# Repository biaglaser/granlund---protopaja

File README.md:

This project was completed for a course at Aalto University and its problem was proposed by 
Granlund OY. It focuses on the development and implementation of an Internet of Things 
(IoT) device designed to monitor structural parameters of network base stations, 
often located in remote and hard-to-reach areas. The device was developed during 
Aalto University’s Protopaja course with the aim is to digitize and automate the 
monitoring and analysis of various structures, products, and services. The primary 
objective was to create an energy-efficient, long-lasting IoT device capable of 
measuring the structural conditions of the station towers and display the collected, 
clean data to the user. 

Utilizing wireless sensor stations, the device aims to capture real-time data and transmit it 
to a microprocessor via Bluetooth. Data is then sent to a cloud-based server via a 
mobile network, where it is processed, stored, and displayed through a user 
interface. This allows for real-time statistical display, anomaly detection, and 
predictive maintenance alerts.

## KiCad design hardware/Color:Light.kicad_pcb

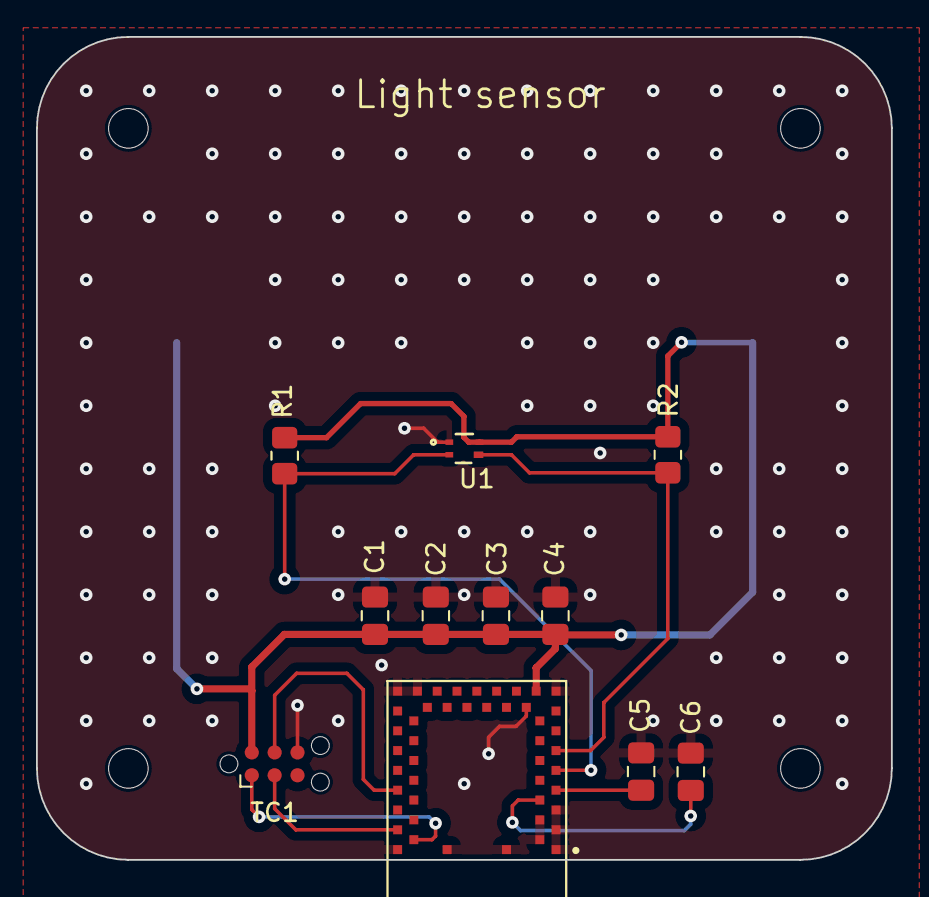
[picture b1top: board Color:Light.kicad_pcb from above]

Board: 2 copper layers, 47.5 x 45.7 mm, 12 parts (1 on the bottom side), 9 nets.

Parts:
BT1: BRX1-2477-SM; BAT_BRX1-2477-SM
C1, C3: 1u; C_0805_2012Metric_Pad1.18x1.45mm_HandSolder
C2: 10u; C_0805_2012Metric_Pad1.18x1.45mm_HandSolder
C4: 100n; C_0805_2012Metric_Pad1.18x1.45mm_HandSolder
C5, C6: 12p; C_0805_2012Metric_Pad1.18x1.45mm_HandSolder
R1, R2: 4.7k; R_0805_2012Metric_Pad1.20x1.40mm_HandSolder
TC1: TC2030-IDC; Tag-Connect_TC2030-IDC-NL_2x03_P1.27mm_Vertical
U1: VEML3328; SMD_L3328_VIS
U2: BMD-301-A-R

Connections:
/RESET: TC1.4, U2.39 (P0.21)
/SCL: R2.2, U1.3, U2.11 (P0.30)
/SDA: R1.2, U1.2, U2.9 (P0.28)
/SW_CLK: TC1.3, U2.43 (SWCLK)
/SW_DIO: TC1.1, U2.44 (SWDIO)
GND: BT1.-, C1.2, C2.2, C3.2, C4.2, C5.2, C6.2, TC1.6, U1.1, U2.1 (GND), U2.2 (GND), U2.3 (GND), U2.4 (GND), U2.5 (GND), U2.16 (GND), U2.18 (GND), U2.29 (GND), U2.30 (GND), U2.45 (GND), U2.46 (GND), U2.47 (GND)
unnamed: C6.1, U2.6 (P0.25)
unnamed: C5.1, U2.7 (P0.26)
VCC: BT1.1+, BT1.2+, C1.1, C2.1, C3.1, C4.1, R1.1, R2.1, TC1.2, U1.4, U2.17 (VCC)

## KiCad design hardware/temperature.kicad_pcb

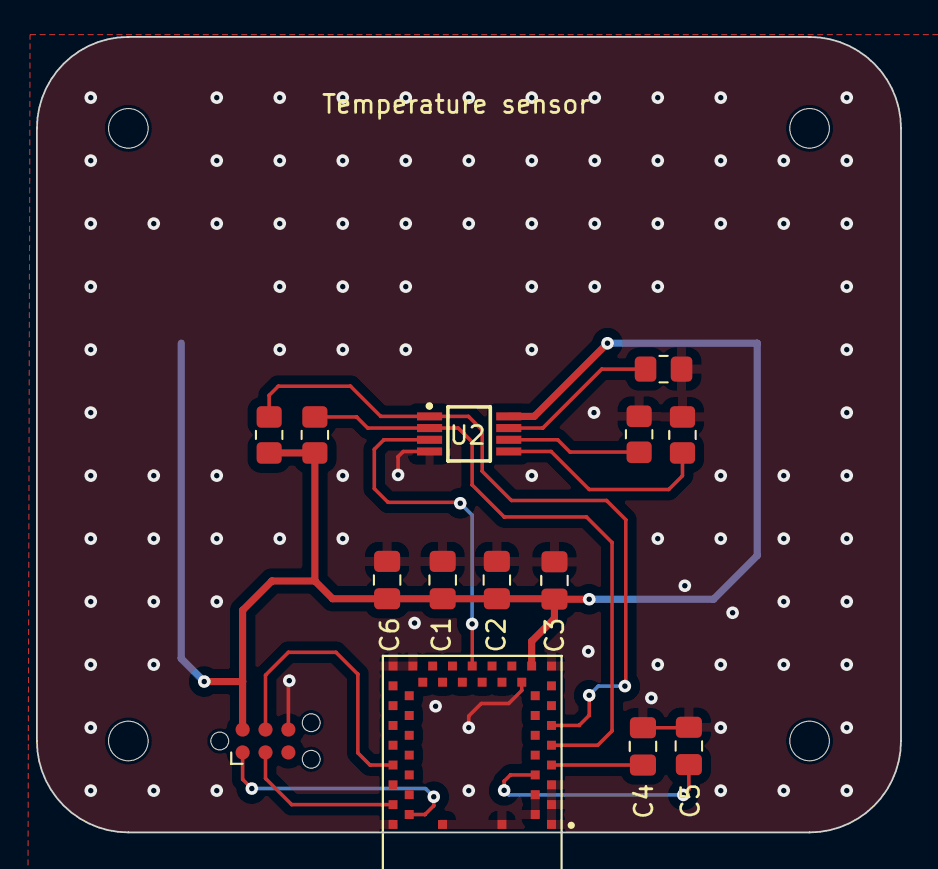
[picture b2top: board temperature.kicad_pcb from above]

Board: 2 copper layers, 48.0 x 44.2 mm, 15 parts (1 on the bottom side), 13 nets.

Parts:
BT2: BRX1-2477-SM; BAT_BRX1-2477-SM
C1: 10u; C_0805_2012Metric_Pad1.18x1.45mm_HandSolder
C2, C6: 1u; C_0805_2012Metric_Pad1.18x1.45mm_HandSolder
C3: 100n; C_0805_2012Metric_Pad1.18x1.45mm_HandSolder
C4, C5: 12p; C_0805_2012Metric_Pad1.18x1.45mm_HandSolder
R6, R7, R8, R9: 4.7k; R_0805_2012Metric_Pad1.20x1.40mm_HandSolder
R10: 4.7K; R_0805_2012Metric_Pad1.20x1.40mm_HandSolder
TC2: TC2030-IDC; Tag-Connect_TC2030-IDC-NL_2x03_P1.27mm_Vertical
U1: BMD-301-A-R
U2: MCP9808T-E/MS; SOP65P490X110-8N

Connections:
/ALERT: U1.23 (P0.07), U2.3 (ALERT)
/RESET: TC2.4, U1.39 (P0.21)
/SCL: R9.2, U1.11 (P0.30), U2.1 (SDA)
/SDA: R10.2, U1.9 (P0.28), U2.2 (SCL)
/SW_CLK: TC2.3, U1.43 (SWCLK)
/SW_DIO: TC2.1, U1.44 (SWDIO)
GND: BT2.-, C1.2, C2.2, C3.2, C4.2, C5.2, C6.1, R6.2, R7.2, R8.2, TC2.6, U1.1 (GND), U1.2 (GND), U1.3 (GND), U1.4 (GND), U1.5 (GND), U1.16 (GND), U1.18 (GND), U1.29 (GND), U1.30 (GND), U1.45 (GND), U1.46 (GND), U1.47 (GND), U2.4 (GND)
unnamed: C5.1, U1.6 (P0.25)
unnamed: C4.1, U1.7 (P0.26)
unnamed: R6.1, U2.7 (A0)
unnamed: R7.1, U2.6 (A1)
unnamed: R8.1, U2.5 (A2)
VCC: BT2.1+, BT2.2+, C1.1, C2.1, C3.1, C6.2, R9.1, R10.1, TC2.2, U1.17 (VCC), U2.8 (VDD)

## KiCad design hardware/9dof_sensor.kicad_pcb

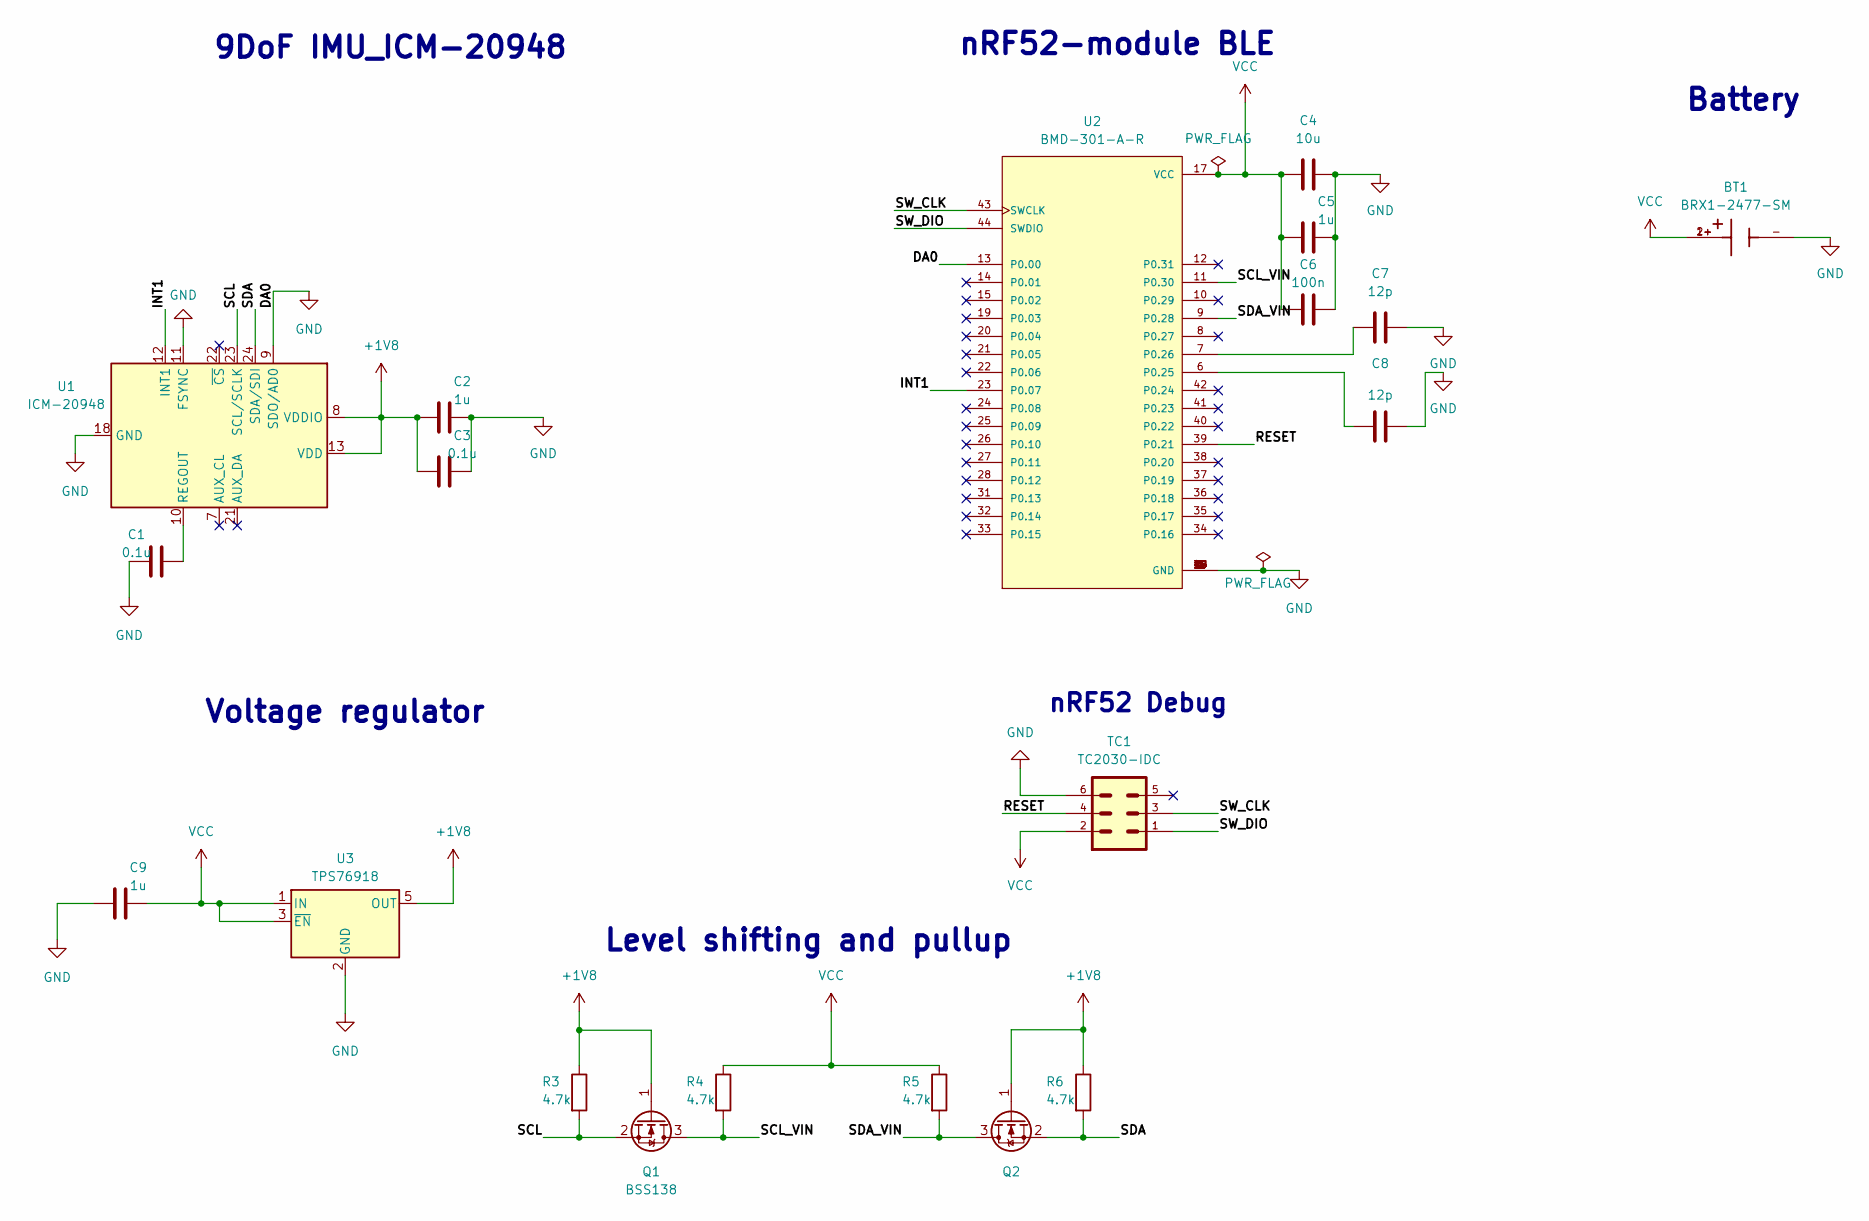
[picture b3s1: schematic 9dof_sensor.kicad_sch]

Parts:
BT1: BRX1-2477-SM; BAT_BRX1-2477-SM; PARTREV D
C1, C3: 0.1u; C_0805_2012Metric_Pad1.18x1.45mm_HandSolder
C2, C5, C9: 1u; C_0805_2012Metric_Pad1.18x1.45mm_HandSolder
C4: 10u; C_0805_2012Metric_Pad1.18x1.45mm_HandSolder
C6: 100n; C_0805_2012Metric_Pad1.18x1.45mm_HandSolder
C7, C8: 12p; C_0805_2012Metric_Pad1.18x1.45mm_HandSolder
Q1, Q2: BSS138; SOT-23
R3, R4, R5, R6: 4.7k; R_0805_2012Metric_Pad1.20x1.40mm_HandSolder
TC1: TC2030-IDC; Tag-Connect_TC2030-IDC-NL_2x03_P1.27mm_Vertical
U1: ICM-20948; InvenSense_QFN-24_3x3mm_P0.4mm
U2: BMD-301-A-R; PARTREV 2.1
U3: TPS76918; SOT-23-5

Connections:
+1V8: C2.1, C3.1, Q1.1 (G), Q2.1 (G), R3.1, R6.1, U1.8 (VDDIO), U1.13 (VDD), U3.5 (OUT)
/INT1: U1.12 (INT1), U2.23 (P0.07)
/RESET: TC1.4, U2.39 (P0.21)
/SCL: Q1.2 (S), R3.2, U1.23 (SCL/SCLK)
/SCL_VIN: Q1.3 (D), R4.2, U2.11 (P0.30)
/SDA: Q2.2 (S), R6.2, U1.24 (SDA/SDI)
/SDA_VIN: Q2.3 (D), R5.2, U2.9 (P0.28)
/SW_CLK: TC1.3, U2.43 (SWCLK)
/SW_DIO: TC1.1, U2.44 (SWDIO)
GND: BT1.-, C1.1, C2.2, C3.2, C4.2, C5.2, C6.2, C7.2, C8.2, C9.1, TC1.6, U1.9 (SDO/AD0), U1.11 (FSYNC), U1.18 (GND), U1.20 (GND), U2.1 (GND), U2.2 (GND), U2.3 (GND), U2.4 (GND), U2.5 (GND), U2.13 (P0.00), U2.16 (GND), U2.18 (GND), U2.29 (GND), U2.30 (GND), U2.45 (GND), U2.46 (GND), U2.47 (GND), U3.2 (GND)
unnamed: C1.2, U1.10 (REGOUT)
unnamed: C8.1, U2.6 (P0.25)
unnamed: C7.1, U2.7 (P0.26)
VCC: BT1.1+, BT1.2+, C4.1, C5.1, C6.1, C9.2, R4.1, R5.1, TC1.2, U2.17 (VCC), U3.1 (IN), U3.3 (~EN)

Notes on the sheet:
Voltage regulator
nRF52-module BLE
9DoF IMU_ICM-20948
nRF52 Debug
Level shifting and pullup
Battery

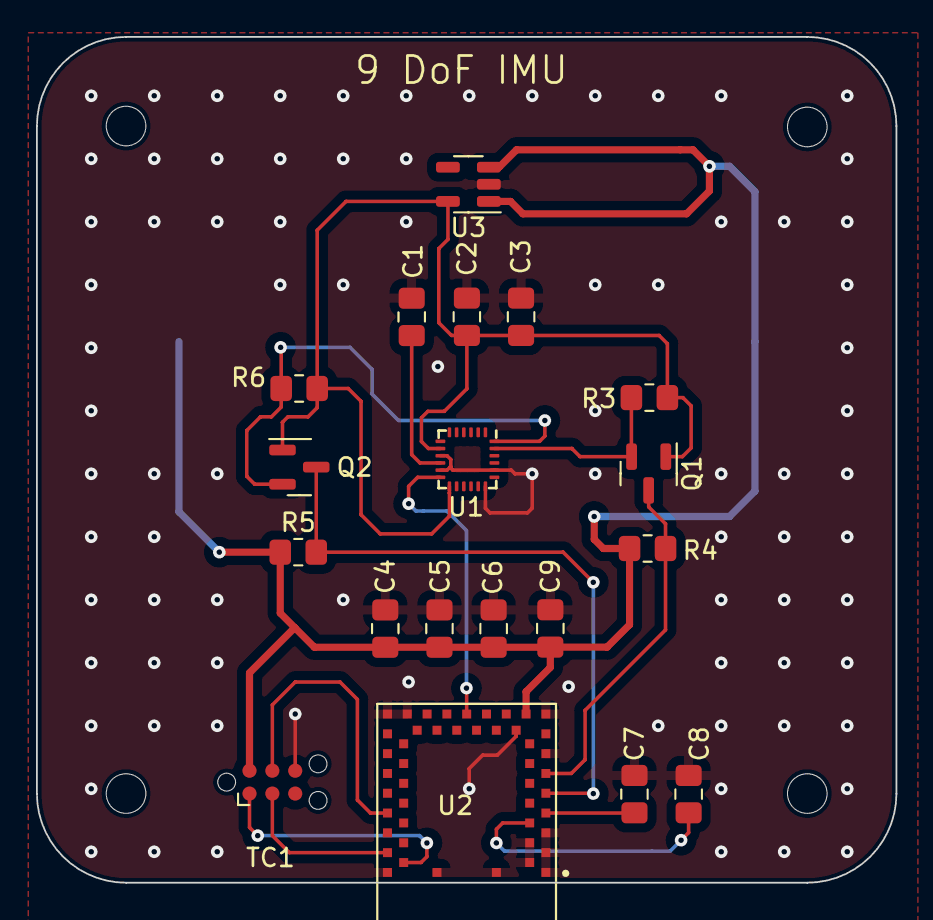
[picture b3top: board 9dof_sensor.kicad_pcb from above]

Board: 2 copper layers, 47.8 x 47.0 mm, 20 parts (1 on the bottom side), 14 nets.

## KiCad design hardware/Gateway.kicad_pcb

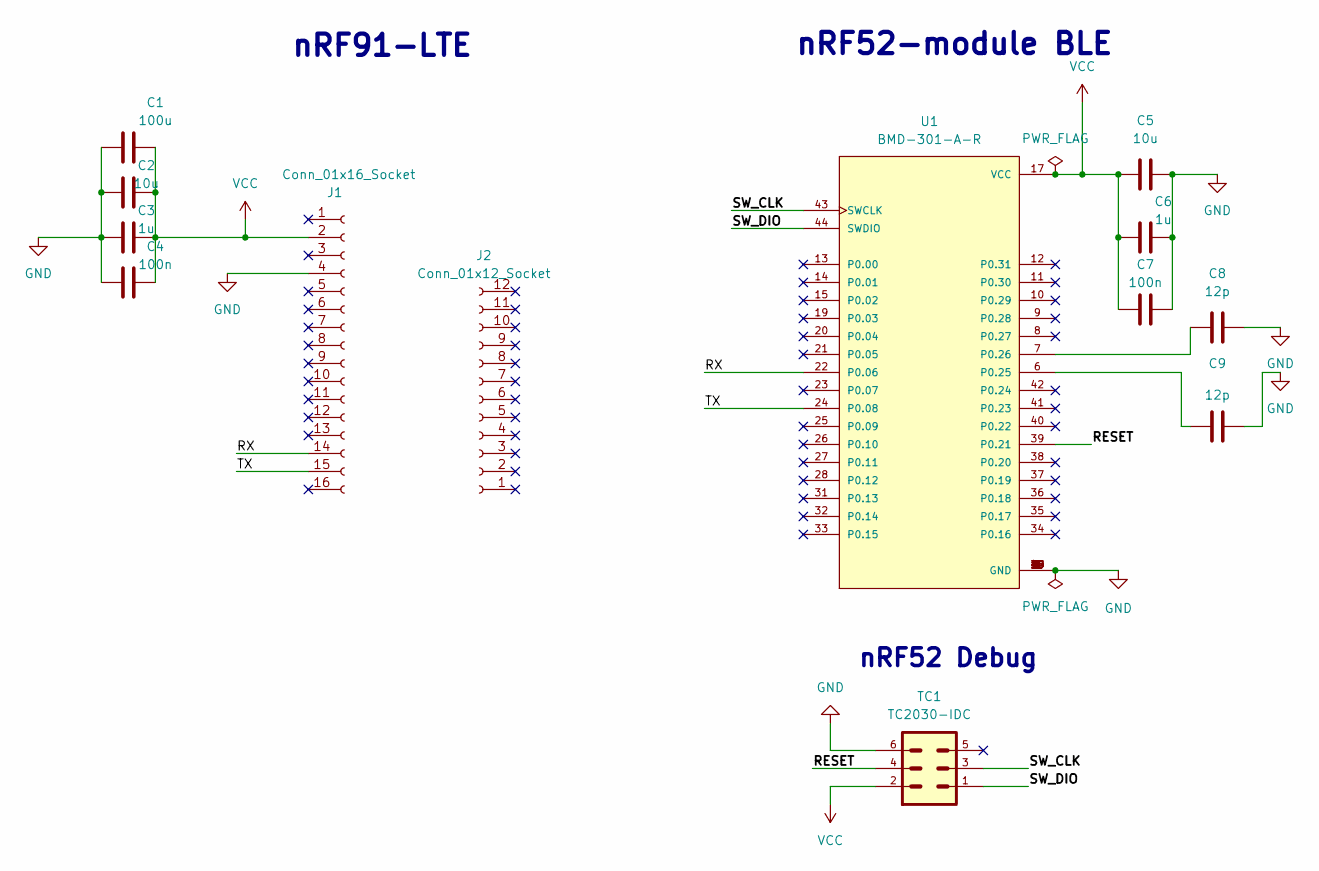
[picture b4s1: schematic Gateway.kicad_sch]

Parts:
C1: 100u; C_1210_3225Metric_Pad1.33x2.70mm_HandSolder
C2, C5: 10u; C_0805_2012Metric_Pad1.18x1.45mm_HandSolder
C3, C6: 1u; C_0805_2012Metric_Pad1.18x1.45mm_HandSolder
C4, C7: 100n; C_0805_2012Metric_Pad1.18x1.45mm_HandSolder
C8, C9: 12p; C_0805_2012Metric_Pad1.18x1.45mm_HandSolder
J1: Conn_01x16_Socket; PinSocket_1x16_P2.54mm_Vertical
J2: Conn_01x12_Socket; PinSocket_1x12_P2.54mm_Vertical
TC1: TC2030-IDC; Tag-Connect_TC2030-IDC-NL_2x03_P1.27mm_Vertical
U1: BMD-301-A-R; PARTREV 2.1

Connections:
/RESET: TC1.4, U1.39 (P0.21)
/RX: J1.14, U1.22 (P0.06)
/SW_CLK: TC1.3, U1.43 (SWCLK)
/SW_DIO: TC1.1, U1.44 (SWDIO)
/TX: J1.15, U1.24 (P0.08)
GND: C1.1, C2.1, C3.1, C4.1, C5.2, C6.2, C7.2, C8.2, C9.2, J1.4, TC1.6, U1.1 (GND), U1.2 (GND), U1.3 (GND), U1.4 (GND), U1.5 (GND), U1.16 (GND), U1.18 (GND), U1.29 (GND), U1.30 (GND), U1.45 (GND), U1.46 (GND), U1.47 (GND)
unnamed: C9.1, U1.6 (P0.25)
unnamed: C8.1, U1.7 (P0.26)
VCC: C1.2, C2.2, C3.2, C4.2, C5.1, C6.1, C7.1, J1.2, TC1.2, U1.17 (VCC)

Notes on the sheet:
nRF52-module BLE
nRF52 Debug
nRF91-LTE

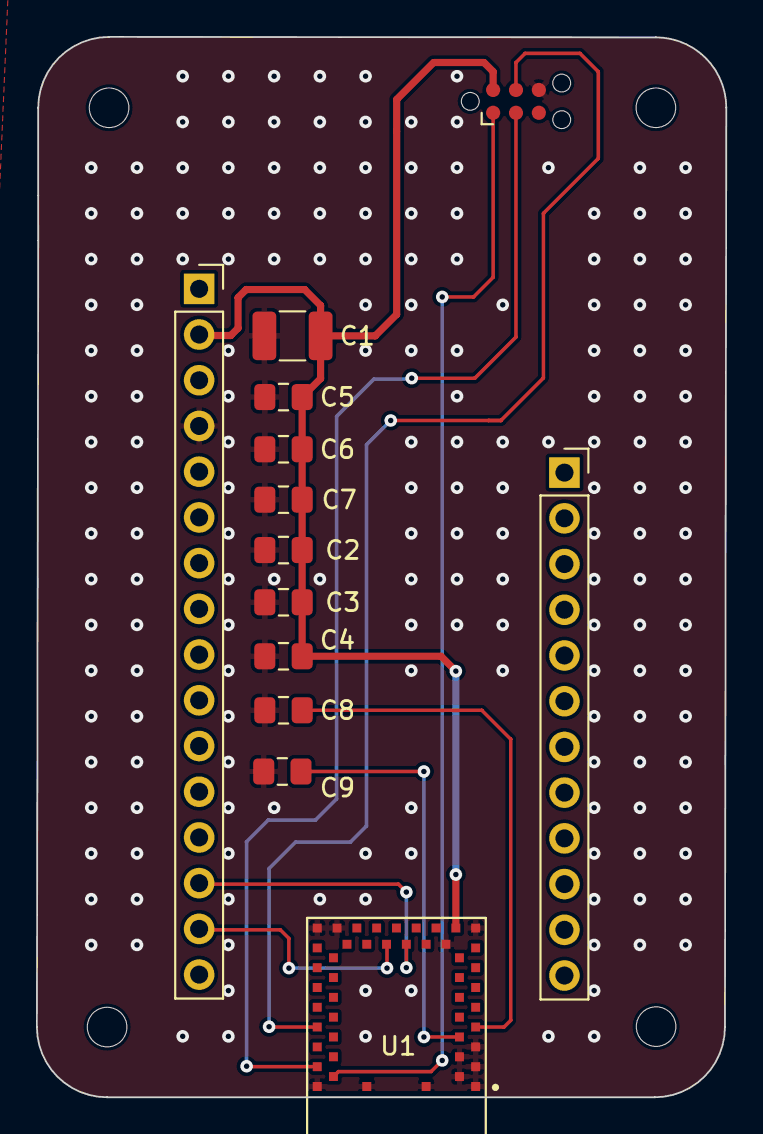
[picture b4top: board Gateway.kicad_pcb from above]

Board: 2 copper layers, 38.3 x 58.9 mm, 13 parts (0 on the bottom side), 9 nets.

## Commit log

2023-08-16 16 august 2023
    Echo_botnrf52 is uploaded to icarus for receiving data from uart . Also can be uploaded to nrf52dk for sending data to uart.
    Broadacster is uploaded to nrf52dk, for advertising BLE beacons. It is not connectable but only scannable.
    Observer is uploaded to gateway's nrf52 to scan beacons and forward the scanned data to uart.
2023-08-16 8 august 2023
    https is uploaded to icarus iot board for making post requests.
2023-08-16 16 august 2023
    https_client. Send http requests to webserver
2023-08-16 Create main.py
    script to run flask app
2023-08-24 Create gateway
2023-08-24 24 august 2023
    Forwarding messages from uart to webserver
2023-08-25 Rename MeasuringAcceleration.ino to sensor station/MeasuringAcceleration.ino
2023-08-25 Rename accel_data_ble.ino to sensor_station/accel_data_ble.ino
